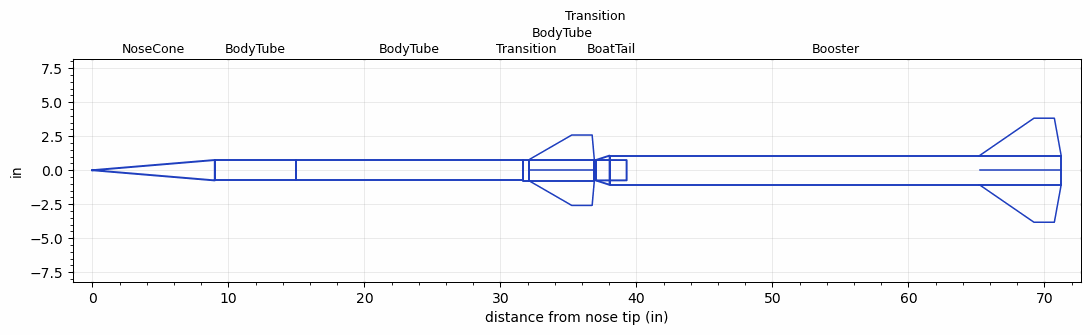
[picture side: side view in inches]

<RASAeroDocument>
 <FileVersion>2</FileVersion>
 <RocketDesign>
  <NoseCone>
   <Length>9</Length>
   <Diameter>1.5</Diameter>
   <Shape>Conical</Shape>
   <Location>0</Location>
  </NoseCone>
  <BodyTube>
   <Length>6</Length>
   <Diameter>1.5</Diameter>
   <Location>9</Location>
  </BodyTube>
  <BodyTube>
   <Length>16.626</Length>
   <Diameter>1.5</Diameter>
   <Location>15</Location>
  </BodyTube>
  <Transition>
   <Length>0.5</Length>
   <Diameter>1.575</Diameter>
   <Location>31.626</Location>
   <RearDiameter>1.575</RearDiameter>
  </Transition>
  <BodyTube>
   <Length>4.778</Length>
   <Diameter>1.575</Diameter>
   <Location>32.126</Location>
   <Fin>
    <Count>4</Count>
    <Chord>4.778</Chord>
    <Span>1.8</Span>
    <SweepDistance>3.118</SweepDistance>
    <TipChord>1.5</TipChord>
    <Thickness>0.1</Thickness>
    <LERadius>0.024</LERadius>
    <Location>4.778</Location>
    <AirfoilSection>Double Wedge</AirfoilSection>
    <FX1>0.75</FX1>
    <FX3>0.25</FX3>
   </Fin>
  </BodyTube>
  <Transition>
   <Length>0.125</Length>
   <Diameter>1.5</Diameter>
   <Location>36.904</Location>
   <RearDiameter>1.5</RearDiameter>
  </Transition>
  <BoatTail>
   <Length>2.25</Length>
   <Diameter>1.5</Diameter>
   <RearDiameter>1.49</RearDiameter>
   <Location>37.029</Location>
  </BoatTail>
  <Booster>
   <Length>33.2</Length>
   <Diameter>2.15</Diameter>
   <InsideDiameter>1.5</InsideDiameter>
   <Location>37.029</Location>
   <ShoulderLength>1</ShoulderLength>
   <Fin>
    <Count>4</Count>
    <Chord>6</Chord>
    <Span>2.75</Span>
    <SweepDistance>4</SweepDistance>
    <TipChord>1.5</TipChord>
    <Thickness>0.157</Thickness>
    <LERadius>0.24</LERadius>
    <Location>6</Location>
    <AirfoilSection>Hexagonal</AirfoilSection>
    <FX1>0.5</FX1>
    <FX3>0.5</FX3>
   </Fin>
  </Booster>
  <Surface>Camouflage Paint</Surface>
  <ModifiedBarrowman>True</ModifiedBarrowman>
  <Turbulence>True</Turbulence>
  <UseBooster1>False</UseBooster1>
  <UseBooster2>False</UseBooster2>
 </RocketDesign>
 <LaunchSite>
  <Altitude>2000</Altitude>
  <Pressure>29.9</Pressure>
  <RodAngle>5</RodAngle>
  <RodLength>10</RodLength>
  <Temperature>110</Temperature>
  <WindSpeed>10</WindSpeed>
 </LaunchSite>
 <Recovery>
  <Altitude1>1000</Altitude1>
  <Altitude2>1000</Altitude2>
  <DeviceType1>None</DeviceType1>
  <DeviceType2>None</DeviceType2>
  <Event1>False</Event1>
  <Event2>False</Event2>
  <Size1>1</Size1>
  <Size2>1</Size2>
  <EventType1>None</EventType1>
  <EventType2>None</EventType2>
  <CD1>1.33</CD1>
  <CD2>1.33</CD2>
 </Recovery>
 <SimulationList>
  <Simulation>
   <SustainerEngine>J360  (Walter)</SustainerEngine>
   <SustainerLaunchWt>3.33</SustainerLaunchWt>
   <SustainerNozzleDiameter>1.325</SustainerNozzleDiameter>
   <SustainerCG>26.62</SustainerCG>
   <SustainerIgnitionDelay>5</SustainerIgnitionDelay>
   <Booster1Engine>L416SW  (Walter)</Booster1Engine>
   <Booster1LaunchWt>9.73</Booster1LaunchWt>
   <Booster1SeparationDelay>0</Booster1SeparationDelay>
   <Booster1IgnitionDelay>0</Booster1IgnitionDelay>
   <Booster1CG>47.6</Booster1CG>
   <Booster1NozzleDiameter>2</Booster1NozzleDiameter>
   <IncludeBooster1>True</IncludeBooster1>
   <Booster2Delay>0</Booster2Delay>
   <IncludeBooster2>False</IncludeBooster2>
   <TimetoApogee>57.97737</TimetoApogee>
   <MaxAltitude>59871.8</MaxAltitude>
   <MaxVelocity>3343.818</MaxVelocity>
   <OptimumWt>3.4965</OptimumWt>
   <OptimumMaxAlt>3.4965</OptimumMaxAlt>
  </Simulation>
  <Simulation>
   <SustainerEngine>J360  (Walter)</SustainerEngine>
   <SustainerLaunchWt>3.33</SustainerLaunchWt>
   <SustainerNozzleDiameter>1.325</SustainerNozzleDiameter>
   <SustainerCG>26.62</SustainerCG>
   <SustainerIgnitionDelay>5</SustainerIgnitionDelay>
   <Booster1Engine>L416SW  (Walter)</Booster1Engine>
   <Booster1LaunchWt>9.75</Booster1LaunchWt>
   <Booster1SeparationDelay>0</Booster1SeparationDelay>
   <Booster1IgnitionDelay>0</Booster1IgnitionDelay>
   <Booster1CG>47.6</Booster1CG>
   <Booster1NozzleDiameter>2</Booster1NozzleDiameter>
   <IncludeBooster1>False</IncludeBooster1>
   <Booster2Delay>0</Booster2Delay>
   <IncludeBooster2>False</IncludeBooster2>
   <TimetoApogee>28.58056</TimetoApogee>
   <MaxAltitude>20649.66</MaxAltitude>
   <MaxVelocity>2174.016</MaxVelocity>
  </Simulation>
 </SimulationList>
</RASAeroDocument>
